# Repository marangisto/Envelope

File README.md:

# Envelope
Eurorack Modular Envelope Generator

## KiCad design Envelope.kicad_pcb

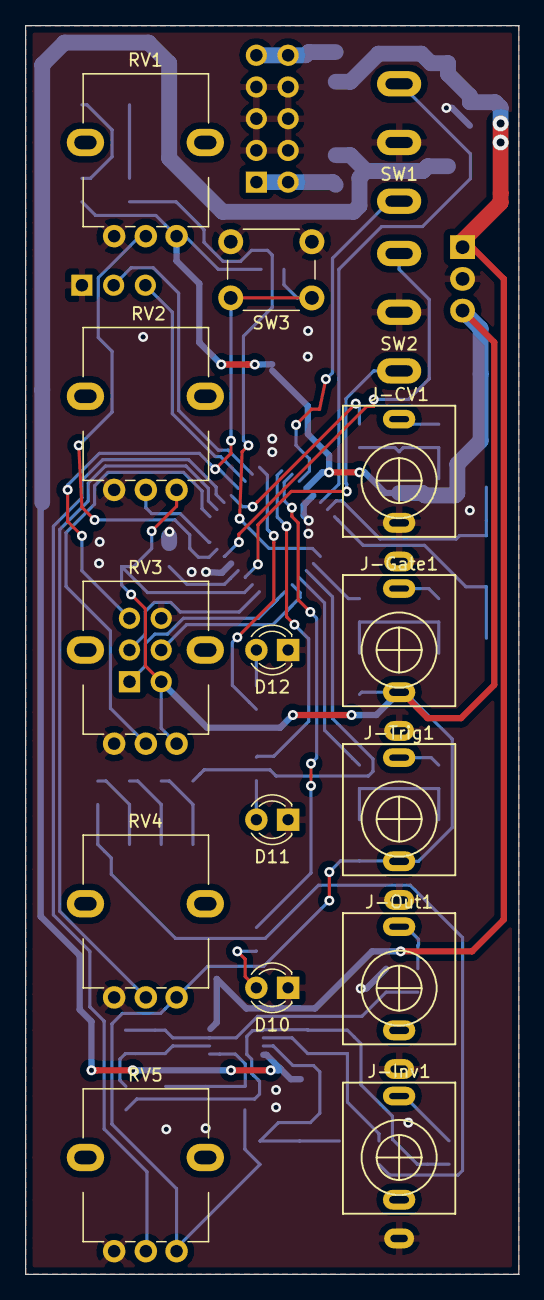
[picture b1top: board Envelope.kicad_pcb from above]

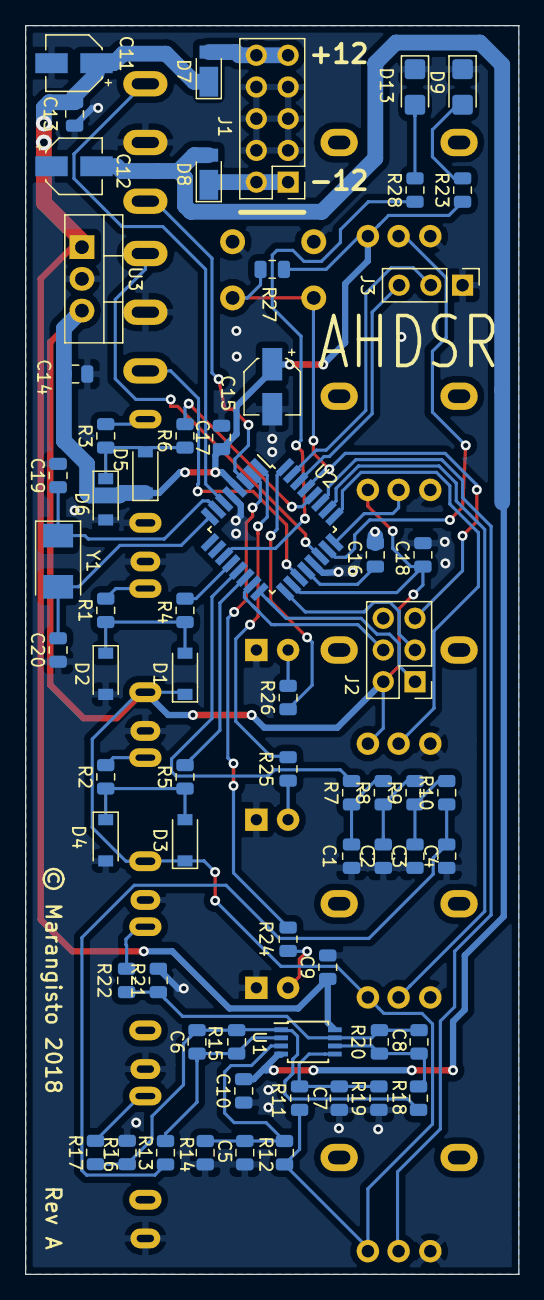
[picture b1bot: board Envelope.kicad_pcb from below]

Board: 2 copper layers, 39.5 x 100.0 mm, 81 parts (65 on the bottom side), 55 nets.

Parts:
C1, C2, C3, C4: 47n; C_0805_2012Metric
C5, C7, C9, C10, C13, C14, C16, C17, C18: 100n; C_0805_2012Metric
C6, C8: 470p; C_0805_2012Metric
C11, C12, C15: 10u; CP_Elec_4x5.8
C19, C20: 22p; C_0805_2012Metric
D1, D2, D3, D4, D5, D6: 1N5819; D_SOD-123
D7, D8: DFLR1400-7; D_PowerDI-123
D9, D13: LED; LED_1206_3216Metric_Castellated
D10, D11, D12: LED; LED_D3.0mm
J1: Conn_02x05_Odd_Even; PinHeader_2x05_P2.54mm_Vertical
J2: Conn_02x03_Odd_Even; PinHeader_2x03_P2.54mm_Vertical
J3: Conn_01x03; PinHeader_1x03_P2.54mm_Vertical
J-CV1: AudioJack2_Ground_Switch; PJ398SM
J-Gate1: AudioJack2_Ground_Switch; PJ398SM
J-Inv1: AudioJack2_Ground_Switch; PJ398SM
J-Out1: AudioJack2_Ground_Switch; PJ398SM
J-Trig1: AudioJack2_Ground_Switch; PJ398SM
R1, R2, R3, R4, R5, R6: 33k; R_0805_2012Metric
R7, R8, R9, R10, R17, R22: 1k; R_0805_2012Metric
R11, R12, R13, R14, R15, R18, R19, R20: 47k; R_0805_2012Metric
R16, R21: 100k; R_0805_2012Metric
R23, R24, R25, R26, R28: 330; R_0805_2012Metric
R27: 10k; R_0805_2012Metric
RV1, RV2, RV3, RV4, RV5: 100k; AlpsRK09K
SW1, SW2: SW_SPDT_MSM; SP1MS1
SW3: SW_Push; SW_PUSH_6mm_H9.5mm
U1: TL072; TSSOP-8_3x3mm_P0.65mm
U2: ATmega328PB-AU; TQFP-32_7x7mm_P0.8mm
U3: L7805; TO-220-3_Vertical
Y1: 20MHz; Crystal_SMD_Abracon_ABM3-2Pin_5.0x3.2mm

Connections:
+5V: C14.1, C15.1, C17.1, C18.2, D1.1, D3.1, D5.1, J2.2, J-Gate1.TN, J-Trig1.TN, R11.2, R12.2, R23.1, R27.1, RV1.1, RV2.1, RV3.1, RV4.1, RV5.1, U2.4, U2.18, U3.3
+12V: C9.1, C11.1, C13.1, D7.1, U1.8, U3.1
-12V: C10.2, C12.2, D8.2, U1.4
/MCU328/PB0: R4.1, U2.12
/MCU328/PB1: R7.2, U2.13
/MCU328/PB2: R5.1, U2.14
/MCU328/PC0: RV1.2, U2.23
/MCU328/PC1: RV2.2, U2.24
/MCU328/PC2: RV3.2, U2.25
/MCU328/PC3: RV4.2, U2.26
/MCU328/PC4: RV5.2, U2.27
/MCU328/PC5: R6.1, U2.28
/MCU328/PD2: R26.1, U2.32
/MCU328/PD3: R25.1, U2.1
/MCU328/PD4: R24.1, U2.2
/MCU328/PD7: R28.1, U2.11
/MCU328/PE0: SW1.1, U2.3
/MCU328/PE1: SW1.3, U2.6
/MCU328/PE2: SW2.1, U2.19
/MCU328/PE3: SW2.3, U2.22
/MCU328/RXD/PD0: J3.3, U2.30
/MCU328/TXD/PD1: J3.2, U2.31
GND: C1.2, C2.2, C3.2, C4.2, C5.2, C7.2, C9.2, C10.1, C11.2, C12.1, C13.2, C14.2, C15.2, C16.1, C17.2, C18.1, C19.1, C20.1, D2.2, D4.2, D6.2, D9.1, D10.1, D11.1, D12.1, D13.1, J1.3, J1.4, J1.5, J1.6, J1.7, J1.8, J2.6, J3.1, J-CV1.S, J-CV1.TN, J-Gate1.S, J-Inv1.S, J-Out1.S, J-Trig1.S, R14.1, R16.2, R19.1, R21.2, RV1.3, RV2.3, RV3.3, RV4.3, RV5.3, SW1.2, SW2.2, SW3.2, U2.5, U2.21, U3.2
unnamed: C1.1, R7.1, R8.2
unnamed: C2.1, R8.1, R9.2
unnamed: C3.1, R9.1, R10.2
unnamed: C4.1, R10.1, R13.2
unnamed: C5.1, R12.1, R14.2, U1.3
unnamed: C6.1, R15.1, R16.1, R17.2, R18.2, U1.1
unnamed: C6.2, R13.1, R15.2, U1.2
unnamed: C7.1, R11.1, R19.2, U1.5
unnamed: C8.1, R20.1, R21.1, R22.2, U1.7
unnamed: C8.2, R18.1, R20.2, U1.6
unnamed: C16.2, U2.20
unnamed: C19.2, U2.7, Y1.1
unnamed: C20.2, U2.8, Y1.2
unnamed: D1.2, D2.1, R1.1, R4.2
unnamed: D3.2, D4.1, R2.1, R5.2
unnamed: D5.2, D6.1, R3.1, R6.2
unnamed: D7.2, J1.9, J1.10
unnamed: D8.1, J1.1, J1.2
unnamed: D9.2, R23.2
unnamed: D10.2, R24.2
unnamed: D11.2, R25.2
unnamed: D12.2, R26.2
unnamed: D13.2, R28.2
unnamed: J2.1, U2.16
unnamed: J2.3, U2.17
unnamed: J2.4, U2.15
unnamed: J2.5, R27.2, SW3.1, U2.29
unnamed: J-CV1.T, R3.2
unnamed: J-Gate1.T, R1.2
unnamed: J-Inv1.T, R17.1
unnamed: J-Out1.T, R22.1
unnamed: J-Trig1.T, R2.2

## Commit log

2018-07-26 Empty schematic and board outline.
2018-07-26 Added reusable AtMega328 subschema.
2018-07-27 More sub-modules.
2018-07-28 Lots of further work.
2018-08-04 Upgraded to KiCad 5.
2018-08-08 Use new jacks.
2018-08-09 Assigned more footprints.
2018-08-16 Finished schema and footprint assignments.
2018-08-16 Panel drawing and initial placement.
2018-08-16 All components place on board but no routing.
2018-08-16 More adjustments on placement.
2018-08-18 Started routing.
2018-08-18 Routed most signals.
2018-08-18 Use 3-pin connector for serial.
2018-08-18 Routed power.
2018-08-18 Corrected position of reset button.
2018-08-18 Completed ground fills.
2018-08-18 Silk screens.
2018-08-18 Added gerbers.
2018-08-19 Connect CV TN to ground to avoid drift.
2018-09-06 Added BOM.
2018-09-06 Reinstated BOM.
2018-09-08 Use csv for BOM.
2018-11-07 Added 3-d models.
2019-05-05 Moved firmware from AVR project.

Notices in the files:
Envelope.kicad_pcb:
© Marangisto 2018
